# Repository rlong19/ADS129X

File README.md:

# ADS129X

Driver and sketches for the Texas Instruments **ADS1299-4 / ADS1299-6 / ADS1299** on a **Teensy 3.6, 4.0, or 4.1**, plus a Classic-Bluetooth sketch for the **original ESP32** (ESP32-WROOM-32E or ESP32-PICO, for example the Adafruit ESP32 Feather V2).

The photographed carrier is a Teensy 4.0 stacked on an **ADS1299-6**. The firmware reads the ID register and uses that channel count. If the ID does not look like an ADS1299, it assumes **6 channels**. Host output is still an **8-channel OpenBCI packet**; channels the chip does not have are zero.

This follows the ADS1299 datasheet (SBAS499C), not the ADS1298 ECG defaults. There is no respiration, pace, or Wilson-terminal register. Address `0x15` is `MISC1` (SRB1). Bias is `BIAS_SENSP` / `BIAS_SENSN`.

## Wiring

SPI is **mode 1** (CPOL = 0, CPHA = 1), MSB first. SCLK is requested at **8 MHz** (the part allows 20 MHz at DVDD >= 2.7 V). `MOSI` drives ADS1299 `DIN`. `MISO` reads `DOUT`.

Tie `CLKSEL` high for the internal 2.048 MHz oscillator, and tie `DAISY_IN` to DGND when this is the only device. `PWDN` and `RESET` are active low. Hold `START` low until the sketch starts conversions. DRDY falls when a new frame is ready; the interrupt is falling-edge.

Analog supplies, the bias resistor network, and SRB1/BIASOUT wiring are on the carrier. The firmware turns the internal 4.5 V reference and the bias amplifier on; it does not create that analog network.

### Teensy 3.6, 4.0, and 4.1

These pins are the same on all three boards and match the stacked carrier used by `Serial_OBCI` (DRDY on 2, PWDN on 3, RESET on 5, START on 6, CS on 10). An earlier loose prototype used a different map (PWDN 2, RESET 3, START 4, DRDY 5, CS 10). Confirm the silk before flashing that older board. Override a pin with `-DADS1299_PIN_DRDY=5` (and the matching `ADS1299_PIN_*` names) or by editing the defaults in `ADS129X.h`.

| Teensy pin | ADS1299 pin | Notes |
| --- | --- | --- |
| 13 (SCK) | SCLK | Hardware SPI. Do not use the onboard LED; it shares this pin. |
| 11 (MOSI) | DIN | |
| 12 (MISO) | DOUT | |
| 10 | CS | Active low, GPIO, not the SPI peripheral's automatic CS. |
| 2 | DRDY | Falling-edge interrupt. |
| 6 | START | Held low during setup, then driven high. |
| 5 | RESET | Active low. Pulsed after the power-up wait. |
| 3 | PWDN | Active low. Driven high to run. |
| GND | DGND, AGND | Common ground. |
| 3.3 V | DVDD | Logic supply. AVDD / AVSS stay on the carrier. |

### Adafruit ESP32 Feather V2 (original ESP32)

This is **not** the stacked Teensy carrier. It is a suggested jumper map for a Feather V2 or any original ESP32 module using these GPIO numbers. ESP32-S2, S3, C3, and C6 are refused: they do not have Bluetooth Classic SPP.

Do not use a DevKit's default VSPI labels (SCK 18, MOSI 23) with this sketch. Wire the GPIOs below. GPIO 34 is input-only and has no internal pull-up; the ADS1299 drives DRDY.

| Feather V2 pin | GPIO | ADS1299 pin |
| --- | --- | --- |
| SCK | 5 | SCLK |
| MO | 19 | DIN |
| MI | 21 | DOUT |
| 33 | 33 | CS |
| A2 | 34 | DRDY |
| 27 | 27 | START |
| A1 | 25 | RESET |
| A0 | 26 | PWDN |
| GND | GND | DGND / AGND |

## What the chip setup does

1. Drive `PWDN` high and hold `RESET` low, then wait 150 ms (`tPOR` is 128 ms at 2.048 MHz; the datasheet's typical power-up is 150 ms).
2. Release `RESET` and wait 18 `tCLK` (~9 µs). The reset low time is longer than the 2 `tCLK` minimum.
3. Send `SDATAC` before any register access. The part wakes in `RDATAC`, and register reads and writes are ignored until `SDATAC`.
4. Read `ID`. `NU_CH` `00` / `01` / `10` means 4 / 6 / 8 channels. Production IDs are usually `0x3C`, `0x3D`, and `0x3E`.
5. `CONFIG1` keeps the reserved bits set (`0x90 | DR`). Data rates are 250 SPS through 16 kSPS. `111` is not used.
6. `CONFIG3` sets bit 7 so the internal reference buffer is on (`0xE0` plus bias bits). The reference start-up wait is 150 ms.
7. Referential sketches close SRB1 (`MISC1 = 0x20`) and put every present channel into `BIAS_SENSP` and `BIAS_SENSN`.
8. `RDATAC`, then the `START` pin goes high. Samples are read on DRDY falling.
9. A frame is 3 status bytes plus 3 bytes per real channel (27 / 21 / 15). Channel data is 24-bit two's complement, sign-extended to 32 bits in `getData()`. Status bits `[23:20]` should read `1100`.

## OpenBCI packets

`Serial_OBCI`, `Serial_EMG`, and `ESP32_SPP` wait for `b` and then write the [Cyton 33-byte frame](https://docs.openbci.com/Cyton/CytonDataFormat/):

| Bytes | Contents |
| --- | --- |
| 0 | `0xA0` |
| 1 | Sample number, 0–255, wrapping |
| 2–25 | Eight 24-bit signed channel values, MSB first |
| 26–31 | Zeros (no accelerometer, so this is not live accel data) |
| 32 | `0xC0` |

The GUI's default scale is `µV = count * (4.5 / 8388607 / gain) * 1e6` with gain 24. `Serial_OBCI` and `ESP32_SPP` use that gain and 250 SPS. `Serial_EMG` uses gain 12 and 2 kSPS, so change the GUI scale before trusting its microvolt axis.

Startup text ends with `$$$`. Commands that answer do so only while streaming is off, so a reply cannot land in the middle of a binary packet.

| Command | Effect |
| --- | --- |
| `b` / `s` | Start or stop the binary stream |
| `v` | Reset the ADS1299, rewrite registers, print the banner |
| `V` | Print `ADS129X-2.0.0$$$` |
| `?` | Read back registers `0x00`–`0x17` |
| `xCHPDGAININBIASSRB2SRB1X` | One channel, same character codes as the Cyton SDK |
| `1`–`8` and `!@#$%^&*` | Power a channel down or up. Powered-down inputs are shorted, and the packet channel is zero |
| `d` / `D` | Restore or report the sketch's default channel template |
| `~0` … `~6` or `~~` | Set or query the data rate (`0` = 16 kSPS … `6` = 250 SPS) |

`z...Z` lead-off commands are consumed so the parser stays aligned, and answered with `not implemented`. Daisy-chain, SD logging, and real accelerometer bytes are not implemented.

## Sketches

| Sketch | Board | Output |
| --- | --- | --- |
| `examples/Serial_OBCI` | Teensy | OpenBCI packets. Referential EEG, gain 24, 250 SPS, SRB1 closed, bias on. |
| `examples/Serial_EMG` | Teensy | OpenBCI packets. Differential inputs, gain 12, 2 kSPS, SRB1 open, bias on. |
| `examples/Serial_Plotter` | Teensy | Eight signed counts, space-separated, for the Arduino Serial Plotter. Same analog setup as `Serial_OBCI`. Starts on its own. |
| `examples/Test_Signal` | Teensy | Same text format. Internal ~2 Hz square wave, gain 1. Expect about ±3495 counts (`VREF/2400` into gain 1). |
| `examples/ESP32_SPP` | Original ESP32 | Same EEG setup as `Serial_OBCI`. Packets on USB serial and Bluetooth SPP name `ADS1299-EEG`. Feather V2 pin map. |
| `examples/ESP32_OpenBCI` | ESP32 and ESP32-S3 dev modules | Same EEG setup, plus WiFi (OpenBCI WiFi Shield HTTP/TCP/UDP) and Bluetooth. See below. |

The first conversions after `START` are sinc-filter settling (about 16 ms at 250 SPS). Status is not a plotter column; `getData()` still returns it in `sample[0]`.

## ESP32 WiFi and Bluetooth

`examples/ESP32_OpenBCI` is the dev-board sketch. It is not the Feather map in `ESP32_SPP`. SPI pins are the Arduino defaults for **ESP32 Dev Module** and **ESP32-S3 Dev Module**, and each one is a `#define` (`ADS_PIN_SCLK`, `ADS_PIN_MISO`, `ADS_PIN_MOSI`, `ADS_PIN_CS`, `ADS_PIN_DRDY`, `ADS_PIN_START`, `ADS_PIN_RESET`, `ADS_PIN_PWDN`) so a different board is a build flag or a one-line edit.

| ADS1299 | ESP32 Dev Module | ESP32-S3 Dev Module |
| --- | --- | --- |
| SCLK | 18 | 12 |
| DIN (MOSI) | 23 | 11 |
| DOUT (MISO) | 19 | 13 |
| CS | 5 | 10 |
| DRDY | 27 | 4 |
| START | 25 | 5 |
| RESET | 26 | 6 |
| PWDN | 32 | 7 |

Leave `STA_SSID` empty and the board starts an access point named `ADS1299-EEG`, password `openbci123`, at **192.168.4.1**. Set `STA_SSID` / `STA_PASSWORD` to join a router instead; if that join fails, it falls back to the same access point. The serial monitor prints the IP. HTTP is port 80.

DRDY is still the sample clock. On ESP32 the GPIO interrupt only wakes a high-priority task (the Arduino SPI driver cannot be called from that interrupt). That task clocks the frame and pushes a 33-byte packet into a 512-deep ring. `loop()` drains the ring onto WiFi and Bluetooth, so a stalled `write` does not have to finish before the next SPI read. `ringDropped()` counts packets that did not fit. The USB line `# ring_dropped=` is printed while USB itself is not streaming binary.

WiFi matches the OpenBCI WiFi Shield enough for BrainFlow and the GUI:

| Request | Role |
| --- | --- |
| `GET /board` | `{"board_connected","board_type":"cyton","num_channels":8,"gains":[...]}` |
| `POST /tcp` | JSON `ip`, `port`, `output` (`raw` or `json`), `delimiter`, `latency`. The ESP32 connects **to that computer** and, once streaming, writes samples. |
| `POST /udp` | Same JSON. One datagram per sample. `"redundancy":true` sends it three times. |
| `POST /command` | `{"command":"~4"}` and the other Cyton ASCII commands. |
| `GET /stream/start` | Starts conversions (`b`). |
| `GET /stream/stop` | Stops them when no other transport still wants samples. |

`raw` output is concatenated 33-byte packets (`0xA0` … `0xC0`). `json` output is one `{"chunk":[{"data":[nanovolts...],"timestamp":...}]}` object per sample, with `\r\n` when `delimiter` is true. BrainFlow asks for `raw`. The `latency` value is accepted and reported; packets are sent on the next `loop()` pass rather than held for that many microseconds.

BrainFlow (the computer listens, the board calls out):

```python
from brainflow.board_shim import BoardShim, BrainFlowInputParams, BoardIds

params = BrainFlowInputParams()
params.ip_address = "192.168.4.1"  # or the STA address printed at boot
params.ip_port = 6677              # free port on this computer
board = BoardShim(BoardIds.CYTON_WIFI_BOARD, params)
board.prepare_session()            # GET /board, POST /tcp, then ~4 (1000 SPS)
board.start_stream()               # GET /stream/start
```

In the OpenBCI GUI choose Cyton over WiFi and enter that IP. `prepare_session` always sends `~4`, so a BrainFlow session runs at **1000 SPS** even though the sketch boots at 250.

Classic Bluetooth SPP is compiled only for the original ESP32 (the S3 has no Classic radio). Pair with `ADS1299-EEG`. The port is a normal serial port: GUI "Cyton (live from serial / dongle)", or BrainFlow `BoardIds.CYTON_BOARD` with `params.serial_port`. Send `b` / `s` as usual.

ESP32-S3 uses BLE Nordic UART under the same name (`6E400001-B5A3-F4F5-A9E5-9E4000000000`). Notifications are 20 bytes so they fit the default ATT MTU; a client has to concatenate them back into 33-byte packets. The OpenBCI GUI does not open a Cyton over BLE. A BLE serial app can send `b` and read the stream.

These rates are from the 33-byte packet and typical radio throughput. They were not measured on hardware.

| Transport | Rate that should fit | Notes |
| --- | --- | --- |
| USB serial at 115200 | 250 SPS | About 11 KB/s on the wire. |
| Classic SPP | 250 SPS, often 1000 | 1000 SPS is 33 KB/s. 2000 SPS is optimistic. |
| BLE notifications | 250 SPS | Two notifications per packet at the default MTU. |
| WiFi TCP | 250 through about 4–8 kSPS | 8 kSPS is about 264 KB/s. 16 kSPS is about 528 KB/s, and the ring is only 32 ms deep at that rate. |
| WiFi UDP | Same order as TCP | Loss is visible as sample-number gaps. Redundancy multiplies the airtime. |

The 512-packet ring is about 2 s at 250 SPS and about 0.5 s at 1000 SPS.

## Build

Install [arduino-cli](https://arduino.github.io/arduino-cli/), then the cores:

```bash
arduino-cli config init
arduino-cli config add board_manager.additional_urls https://www.pjrc.com/teensy/package_teensy_index.json
arduino-cli config add board_manager.additional_urls https://espressif.github.io/arduino-esp32/package_esp32_index.json
arduino-cli core update-index
arduino-cli core install teensy:avr
arduino-cli core install esp32:esp32
```

From a checkout of this repository (the folder that contains `ADS129X.h`):

```bash
mkdir -p /tmp/ardulibs
ln -sfn "$PWD" /tmp/ardulibs/ADS129X

arduino-cli compile --fqbn teensy:avr:teensy40 --libraries /tmp/ardulibs examples/Serial_OBCI
arduino-cli compile --fqbn teensy:avr:teensy41 --libraries /tmp/ardulibs examples/Serial_OBCI
arduino-cli compile --fqbn teensy:avr:teensy36 --libraries /tmp/ardulibs examples/Serial_OBCI

arduino-cli compile --fqbn teensy:avr:teensy40 --libraries /tmp/ardulibs examples/Serial_EMG
arduino-cli compile --fqbn teensy:avr:teensy40 --libraries /tmp/ardulibs examples/Serial_Plotter
arduino-cli compile --fqbn teensy:avr:teensy40 --libraries /tmp/ardulibs examples/Test_Signal

arduino-cli compile --fqbn esp32:esp32:adafruit_feather_esp32_v2 --libraries /tmp/ardulibs examples/ESP32_SPP

# Default 1.2 MB app partition is too small for WiFi + Bluetooth.
# Huge APP is 3 MB and has no OTA slot. Minimal SPIFFS (1.9 MB) also fits.
arduino-cli compile --fqbn esp32:esp32:esp32:PartitionScheme=huge_app --libraries /tmp/ardulibs examples/ESP32_OpenBCI
arduino-cli compile --fqbn esp32:esp32:esp32s3:PartitionScheme=huge_app --libraries /tmp/ardulibs examples/ESP32_OpenBCI
```

In the Arduino IDE, install **Teensy (for Arduino IDE 2.x)** and **esp32** by Espressif, then open a sketch from `examples/`. Pick Teensy 4.0, 4.1, or 3.6, **Adafruit Feather ESP32 V2** for `ESP32_SPP`, or **ESP32 Dev Module** / **ESP32S3 Dev Module** for `ESP32_OpenBCI`. For that last sketch set **Tools → Partition Scheme → Huge APP (3MB No OTA/1MB SPIFFS)**. USB serial on the Feather and on Dev Modules is 115200. Teensy USB serial ignores the baud number.

`examples/ESP32_SPP` does not compile for ESP32-S2/S3/C3/C6 on purpose. `examples/ESP32_OpenBCI` compiles for the original ESP32 and the ESP32-S3.

Checked with arduino-cli, Teensy core 1.62.0, and ESP32 core 3.3.12. No ADS1299 was attached.

| Sketch | Teensy 4.0 | Teensy 4.1 | Teensy 3.6 | Feather ESP32 V2 | ESP32 Dev Module | ESP32-S3 Dev Module |
| --- | --- | --- | --- | --- | --- | --- |
| Serial_OBCI | yes | yes | yes | | | |
| Serial_EMG | yes | yes | yes | | | |
| Serial_Plotter | yes | yes | yes | | | |
| Test_Signal | yes | yes | yes | | | |
| ESP32_SPP | | | | yes | yes | |
| ESP32_OpenBCI | | | | | yes (Huge APP) | yes (Huge APP) |

The same four Teensy sketches also compiled for Teensy 3.2 / 3.1 (`teensy:avr:teensy31`). Adafruit Feather ESP32-S3 stops in `ESP32_SPP` with the Classic-Bluetooth error. A Dev Module build of `ESP32_SPP` still uses the Feather GPIO numbers in the wiring table above. `ESP32_OpenBCI` on a Dev Module uses the dev-board pins in the ESP32 section.

Nothing in this tree was run on the carrier. Confirm the ID line (`0x3D` for an ADS1299-6), that status bits `[23:20]` are `1100`, and that the test-signal sketch steps by about ±3495 counts before trusting electrode data.

## License

MIT. See [LICENSE.md](LICENSE.md). Original ADS1299 code by Conor Russomanno; the earlier Arduino port by Ferdinand Keil.

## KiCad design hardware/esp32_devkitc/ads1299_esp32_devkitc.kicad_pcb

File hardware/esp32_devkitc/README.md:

# ADS1299 carrier for the ESP32-DevKitC-32

Carrier for an ADS1299 (the built board is stuffed as an ADS1299-6) and a HiLetgo / Espressif ESP32-DevKitC-32 (ESP32-WROOM-32, 38-pin, 2×19). It replaces the Teensy 4.0 carrier. The DevKit plugs into two 1×11 sockets. Its USB port is the serial link, so the old RX/TX/GND/5V header is gone and the electrode side is a single 0.1 inch column.

The layout is KiCad 8.0.9 (`kicad_pcb` version 20240108). KiCad 8 opens it. KiCad 7 does not.

**Do not send this revision to a fab.** The SPI and control nets are routed. The analog supply, the reference caps, and two of the electrode nets are still open, and DRC is not clean. Details are below.

## Size

|  | Teensy carrier | This board |
| --- | --- | --- |
| Outline | 36.83 × 46.99 mm | 31.3 × 32.0 mm bounding box |
| Copper area | about 1731 mm² | about 886 mm² |

The outline is the DevKit width plus a 2.9 mm tab. The main rectangle is 28.4 mm wide. The tab (x = 28.4 to 31.3 mm, y = 0 to 15.6 mm) holds J1. The antenna end of the DevKit lines up with the top edge of this board and overhangs it; that overhang is clear of copper.

## What changed from the Teensy board

- Teensy 4.0 sockets (two rows, 15.24 mm apart, 14 pins) are replaced by DevKitC sockets (two rows, **25.40 mm** apart, 11 pins of the 19).
- The 1×4 RX/TX/GND/5V header is removed. USB on the DevKit is the serial port.
- The 2×14 electrode breakout is a 1×6 column: the three-snap wiring plus analog 5 V and ground.
- No 3.3 V regulator on the carrier, same as the Teensy board. DVDD comes from the DevKit 3V3 pin.
- Analog supply stays a single unipolar 5 V rail. No input filters were added.

## ESP32 wiring

Socket pin 1 is the antenna end. Only pins 1–11 are on this board. Pins 12–19 and the USB connector hang off the bottom.

These match `examples/ESP32_OpenBCI/ESP32_OpenBCI.ino` for the ESP32 Dev Module.

| DevKit pin | GPIO | ADS1299 |
| --- | --- | --- |
| J2.1 | 3V3 | DVDD |
| J2.7 | 32 | PWDN |
| J2.9 | 25 | START |
| J2.10 | 26 | RESET |
| J2.11 | 27 | DRDY |
| J3.1 and J3.7 | GND | GND |
| J3.2 | 23 | DIN (MOSI) |
| J3.8 | 19 | DOUT (MISO) |
| J3.9 | 18 | SCLK |
| J3.10 | 5 | CS |

J2 EN, VP, VN, IO34, IO35, IO33 and J3 IO22, TX, RX, IO21, IO17 are drilled so the DevKit can plug in. They are not connected. TX and RX are not wired; use the DevKit USB connector.

Power the DevKit from its USB port. Do not connect the DevKit 5V pin to the analog 5 V rail. The two grounds are common.

## J1, bottom to top

| Pin | Net | Three-snap use |
| --- | --- | --- |
| 1 | IN1P | signal (EEG or EMG+) |
| 2 | IN1N | EMG−. Leave open for referential EEG |
| 3 | SRB1 | EEG reference |
| 4 | BIASOUT | bias electrode |
| 5 | GND | boost-module ground |
| 6 | AVDD | analog 5 V from the LiPo boost |

Referential EEG: signal on pin 1, reference on pin 3, bias on pin 4. Differential EMG: pins 1, 2, and 4.

## Analog circuit

Unipolar, ADS1299 datasheet Figure 77 style:

- AVDD = 5 V from J1 pin 6 only. AVSS, AVSS1, DGND, VREFN, and RESV1 are the one ground net.
- DVDD = 3.3 V from J2 pin 1.
- CLK is tied to ground. CLKSEL is pulled to DVDD with R2 (10 kΩ) so the internal 2.048 MHz oscillator runs.
- DAISY_IN is tied to ground.
- GPIO1–GPIO4 each have a 10 kΩ pulldown. The firmware does not use them.
- IN7 and IN8 (pins 1–4) are tied to AVDD because the ADS1299-6 has no channels 7 and 8. Cut those ties to stuff an ADS1299-8. Channels 2–6 are left open, which is the same as an unplugged header pin.
- BIASOUT to BIASINV is R1 1 MΩ in parallel with C13 10 nF. That network is an assumption: the original silkscreen values were only partly readable. BIASIN and BIASREF are not connected. SRB2 is not connected.
- Bypass: C1 10 µF and C2 100 nF on AVDD, C3 1 µF on AVDD1, C4 1 µF and C5 100 nF on DVDD, C6 10 µF and C7 100 nF on VREFP, C8 100 µF on VCAP1, C9 1 µF on VCAP2, C10 1 µF and C11 100 nF on VCAP3, C12 1 µF on VCAP4. All returns go to ground.

The PAG package on this footprint has no exposed pad. Ground is the AVSS, AVSS1, DGND, and RESV1 pins, each via-stitched to the bottom plane where a hole fits.

## Ground plane

One bottom-copper zone covers the outline, pulled in 0.30 mm from the edge. Nothing is placed under the 10 mm package body, and no track is routed under that body on either layer. The exposed-pad area does not exist on this package; the ground pins drop to the plane on short top-side traces and vias just outside the body.

SPI (DRDY, START, RESET, PWDN, DOUT, SCLK, CS) crosses the board on the bottom only north of the package, then drops beside the DevKit sockets. Those bottom runs are kept out of the analog input and reference region. A few other bottom runs (electrode drops in the tab, and unfinished VCAP stubs beside the package) are outside the package body. They are a compromise so those nets can reach a header without crossing the top-side fanout, and they are subtracted from the pour.

Digital return current stays on the top fanout and on those northern bottom jumpers, not across the input pins.

## DRC (KiCad 8.0.9)

`kicad-cli pcb drc --severity-error` on this board:

| | Count |
| --- | --- |
| Shorts | 0 |
| Clearance | 20 |
| Unconnected items | 32 |
| Hole-to-hole | 3 |
| Hole clearance | 1 |
| Solder-mask bridge | 1 |

Nets that are one copper piece today: DRDY, START, RESET, PWDN, DIN, DOUT, SCLK, CS, and IN1N.

Still more than one piece: DVDD, AVDD, AVDD1, VREFP, VCAP1–VCAP4, IN1P, SRB1, BIASOUT, BIASINV, CLKSEL. Many of the GND “unconnected” DRC hits are SMD pads that do not yet have a via into the plane. The pour ties the plated holes.

Rules used: 0.15 mm clearance, 0.20 mm tracks (0.15 mm in the 0.5 mm fanout), 0.25 mm copper-to-edge, 0.45 mm hole-edge to hole-edge. The solder-mask minimum web is set to 0 because a 0.5 mm QFP cannot keep a mask web between pads.

## Check before any order

1. Caliper the DevKit you actually have. This board uses the Espressif DevKitC V4 drawing: **25.40 mm** row spacing, 27.94 × 48.26 mm PCB, pin 1 1.30 mm from the antenna edge, antenna metal 6.04 mm past that edge. A “breadboard friendly” WROOM-32 clone is often 22.86 mm (0.9 in) between rows and will not plug in. HiLetgo’s listing does not print the row spacing.
2. Do not order this revision until the open analog nets above are finished and DRC is re-run.
3. Confirm the bias network (1 MΩ || 10 nF) against the board you are copying. BIASREF and BIASIN are unconnected here.
4. Analog 5 V is only J1 pin 6. The boost module ground is J1 pin 5. Do not use the DevKit 5V pin for the ADS1299.
5. The file is KiCad 8. Opening it in KiCad 7 will fail.

## Files

- `ads1299_esp32_devkitc.kicad_pro`, `.kicad_sch`, `.kicad_pcb`
- `build_board.py` regenerates the PCB with KiCad 8’s `pcbnew` module
- `gerber/` — F.Cu, B.Cu, F/B silk, F/B mask, Edge.Cuts, Excellon drill in millimetres
- `plots/ads1299_esp32_devkitc.png` — front copper, back copper, front silk, and the board edge

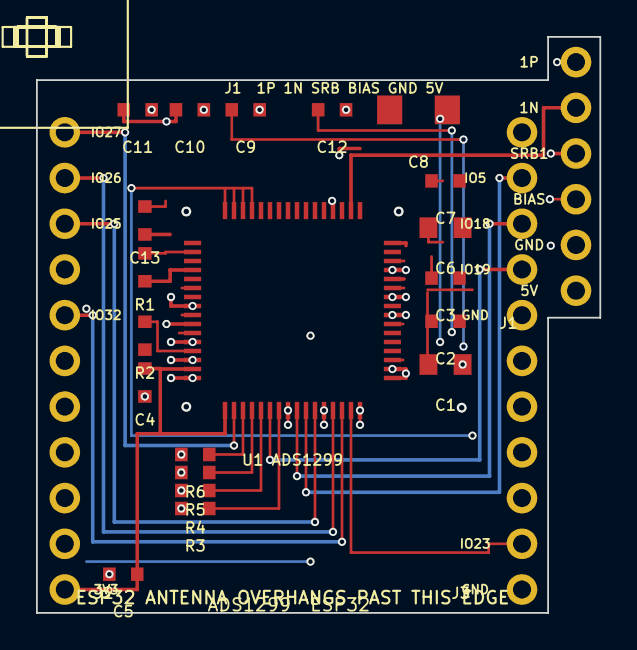
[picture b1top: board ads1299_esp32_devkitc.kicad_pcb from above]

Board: 2 copper layers, 31.3 x 32.0 mm, 23 parts (0 on the bottom side), 27 nets.

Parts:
C1, C6: 10uF
C2, C5, C7, C11: 100nF
C3, C4, C9, C10, C12: 1uF
C8: 100uF
C13: 10nF
J1: Electrode_5V_1x6
J2: ESP32_J2_1x11
J3: ESP32_J3_1x11
R1: 1M
R2, R3, R4, R5, R6: 10k
U1 ADS1299: ADS1299

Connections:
AVDD: C1.1, C2.1, J1.6, U1 ADS1299.1, U1 ADS1299.2, U1 ADS1299.3, U1 ADS1299.4, U1 ADS1299.19, U1 ADS1299.21, U1 ADS1299.22, U1 ADS1299.56, U1 ADS1299.59
AVDD1: C3.1, U1 ADS1299.54
BIASINV: C13.2, R1.2, U1 ADS1299.61
BIASOUT: C13.1, J1.4, R1.1, U1 ADS1299.63
CLKSEL: R2.1, U1 ADS1299.52
CS: J3.10, U1 ADS1299.39
DIN: J3.2, U1 ADS1299.34
DOUT: J3.8, U1 ADS1299.43
DRDY: J2.11, U1 ADS1299.47
DVDD: C4.1, C5.2, J2.1, R2.2, U1 ADS1299.48, U1 ADS1299.50
GND: C1.2, C2.2, C3.2, C4.2, C5.1, C6.2, C7.2, C8.2, C9.2, C10.2, C11.2, C12.2, J1.5, J3.1, J3.7, R3.1, R4.1, R5.1, R6.1, U1 ADS1299.20, U1 ADS1299.23, U1 ADS1299.25, U1 ADS1299.31, U1 ADS1299.32, U1 ADS1299.33, U1 ADS1299.37, U1 ADS1299.41, U1 ADS1299.49, U1 ADS1299.51, U1 ADS1299.53, U1 ADS1299.57, U1 ADS1299.58
GPIO1: R3.2, U1 ADS1299.42
GPIO2: R4.2, U1 ADS1299.44
GPIO3: R5.2, U1 ADS1299.45
GPIO4: R6.2, U1 ADS1299.46
IN1N: J1.2, U1 ADS1299.15
IN1P: J1.1, U1 ADS1299.16
PWDN: J2.7, U1 ADS1299.35
RESET: J2.10, U1 ADS1299.36
SCLK: J3.9, U1 ADS1299.40
SRB1: J1.3, U1 ADS1299.17
START: J2.9, U1 ADS1299.38
VCAP1: C8.1, U1 ADS1299.28
VCAP2: C9.1, U1 ADS1299.30
VCAP3: C10.1, C11.1, U1 ADS1299.55
VCAP4: C12.1, U1 ADS1299.26
VREFP: C6.1, C7.1, U1 ADS1299.24

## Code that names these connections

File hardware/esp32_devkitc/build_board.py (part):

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    23: "AVSS", 24: "VREFP", 25: "VREFN", 26: "VCAP4", 27: "NC", 28: "VCAP1",
    29: "NC", 30: "VCAP2", 31: "RESV1", 32: "AVSS",
    33: "DGND", 34: "DIN", 35: "PWDN", 36: "RESET", 37: "CLK", 38: "START",
    39: "CS", 40: "SCLK", 41: "DAISY_IN", 42: "GPIO1", 43: "DOUT", 44: "GPIO2",
    45: "GPIO3", 46: "GPIO4", 47: "DRDY", 48: "DVDD",
    49: "DGND", 50: "DVDD", 51: "DGND", 52: "CLKSEL", 53: "AVSS1", 54: "AVDD1",
    55: "VCAP3", 56: "AVDD", 57: "AVSS", 58: "AVSS", 59: "AVDD", 60: "BIASREF",
    61: "BIASINV", 62: "BIASIN", 63: "BIASOUT", 64: "RESERVED",
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PIN_NET[41] = "GND"  # DAISY_IN
# IN7/IN8 do not exist on the ADS1299-6; datasheet: unused inputs to AVDD.
for i in (1, 2, 3, 4):
    PIN_NET[i] = "AVDD"
PIN_NET[27] = "NC27"
PIN_NET[29] = "NC29"
PIN_NET[64] = "NC64"
# GPIO pulldowns are separate nets on the pin, resistor to GND.
for i, name in ((42, "GPIO1"), (44, "GPIO2"), (45, "GPIO3"), (46, "GPIO4")):
    PIN_NET[i] = name


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# VCAP3 caps sit below the package, left of the other reservoir caps.
add_two("C11", "100nF", 5.6, 4.05, 1.55, 0, 0.7, 0.75, "VCAP3", "GND")
add_two("C10", "1uF", 8.5, 4.05, 1.55, 0, 0.7, 0.75, "VCAP3", "GND")
# DVDD bulk near the ESP32 3V3 pin, above the digital fanout.
add_two("C5", "100nF", 4.8, 29.85, 1.55, 0, 0.7, 0.75, "GND", "DVDD")
# GPIO pulldowns on their fanout lanes. Right pad is the GPIO net.
add_two("R6", "10k", 8.8, 23.20, 1.55, 0, 0.7, 0.75, "GND", "GPIO4")
add_two("R5", "10k", 8.8, 24.20, 1.55, 0, 0.7, 0.75, "GND", "GPIO3")
add_two("R4", "10k", 8.8, 25.20, 1.55, 0, 0.7, 0.75, "GND", "GPIO2")
add_two("R3", "10k", 8.8, 26.20, 1.55, 0, 0.7, 0.75, "GND", "GPIO1")

add_two("C1", "10uF", 22.7, 18.2, 1.9, 0, 1.0, 1.15, "AVDD", "GND", 0.8)
add_two("C2", "100nF", 22.7, 15.8, 1.55, 0, 0.7, 0.75, "AVDD", "GND")
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wire("DIN", [(17.45, 20.75), (17.45, 28.65), (25.10, 28.65), (25.10, hy(1)), (RIGHT_X, hy(1))], width=0.15)

# GPIO pulldowns. Right pad of each resistor is the GPIO net (x=9.575).
wire("GPIO4", [(11.45, 20.75), (11.45, 23.20), (9.575, 23.20)], width=0.15)
wire("GPIO3", [(11.95, 20.75), (11.95, 24.20), (9.575, 24.20)], width=0.15)
wire("GPIO2", [(12.45, 20.75), (12.45, 25.20), (9.575, 25.20)], width=0.15)
wire("GPIO1", [(13.45, 20.75), (13.45, 26.20), (9.575, 26.20)], width=0.15)

# DVDD: both package pins, C4, C5, and J2 3V3. Not the DevKit 5V pin.
wire("DVDD", [(10.45, 20.75), (10.45, 22.05), (6.85, 22.05), (6.85, 18.425), (6.00, 18.425)], width=0.20)
wire("DVDD", [(8.65, 18.45), (6.85, 18.45)])
wire("DVDD", [(LEFT_X, hy(0)), (5.575, hy(0)), (5.575, 29.85)])
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svia(15.20, 16.60)
wire("AVDD1", [(15.20, 16.60), (15.20, 12.20), (21.925, 12.20), (21.925, 13.40)], width=0.15)

# Right-hand AVDD pins to C1, C2, and the 5 V tab pin.
wire("AVDD", [(19.75, 13.95), (20.40, 13.95), (20.40, 14.20), (21.70, 14.20), (21.70, 18.20), (21.75, 18.20)], width=0.15)
wire("AVDD", [(19.75, 13.45), (20.40, 13.45)])
wire("AVDD", [(19.75, 12.45), (20.40, 12.45), (20.40, 14.05), (ELEC_X, 14.05), (ELEC_X, 14.10)], width=0.15)
wire("AVDD", [(21.70, 15.80), (21.925, 15.80)], width=0.15)
# Left AVDD pins and the IN7/IN8 ties (ADS1299-6 has no channels 7-8).
wire("AVDD", [(8.65, 15.45), (8.05, 15.45), (8.05, 8.40)], width=0.15)
wire("AVDD", [(8.65, 13.95), (8.05, 13.95)], width=0.15)
wire("AVDD", [(10.45, 9.65), (10.45, 8.40)], width=0.15)
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
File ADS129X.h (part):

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#endif

namespace ADS1299Board {
static const int DRDY = ADS1299_PIN_DRDY;
static const int PWDN = ADS1299_PIN_PWDN;
static const int RESET = ADS1299_PIN_RESET;
static const int START = ADS1299_PIN_START;
static const int CS = ADS1299_PIN_CS;
static const int SCLK = ADS1299_PIN_SCLK; // Teensy SCK / ESP32 SCK
static const int DIN = ADS1299_PIN_DIN;   // MOSI -> ADS1299 DIN
static const int DOUT = ADS1299_PIN_DOUT; // MISO <- ADS1299 DOUT
}

// SPI commands (SBAS499C Table 10).
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static const uint8_t ADS1299_REG_LOFF_STATP = 0x12;
static const uint8_t ADS1299_REG_LOFF_STATN = 0x13;
static const uint8_t ADS1299_REG_GPIO = 0x14;
static const uint8_t ADS1299_REG_MISC1 = 0x15; // bit 5 = SRB1
static const uint8_t ADS1299_REG_MISC2 = 0x16;
static const uint8_t ADS1299_REG_CONFIG4 = 0x17;
static const uint8_t ADS1299_REG_COUNT = 24;
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
class ADS129X {
public:
    // Pass -1 for reset, pwdn, or start if that pin is strapped on the board
    // and is not driven by the microcontroller.
    ADS129X(int drdy, int cs, int reset = -1, int pwdn = -1, int start = -1);

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    void WAKEUP();
    void STANDBY();
    void RESET(); // software or pin reset, then rewrite the cached registers
    void START(); // START pin high, or START command if no pin, then DRDY
    void STOP();
    void RDATAC();
    void SDATAC();
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
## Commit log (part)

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2019-10-11 Update ADS129X.h
    Added support for ADS1299
2019-10-11 Update Serial_OBCI.ino
    Added support for ADS1299 and Teensy 4.0
2019-10-11 Reference hardware image and Serial Plotter screenshot.
    Image of prototype using Paul Stoffregen's Biopotential Library reference hardware https://oshpark.com/shared_projects/FCVCtANz
    and screenshot of Serial Plotter output.
2019-10-11 Update README.md
    Added support for the Biopotential Signal Library reference hardware and ADS1299 + Teensy 4.0.
2019-11-25 Add files via upload
    Updated support for ADS1299, changed all "digitalWrite()" to "digitalWriteFast()" for more stable SPI transfers at high speed. 16KSPS now working on Teensy 4.0 at 600Mhz.
2019-11-25 Changes to support 16KSPS. Output in nanoVolts.
    Support for ADS1299 at 16KSPS and ADS1298 at 32KSPS. Output to serial is now converted to double from Int32, and is scaled in nanoVolts. Calculation of 1000 sample average offset which is used to aut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
